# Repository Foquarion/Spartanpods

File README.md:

# Spartanpods Logo PCB Variations
Use Version 2 as the production model

# Version Description:
  - Version 1 is the original wave text version
  - Version 2 is the SQUARE PCB version (USE THIS ONE)
  - Version 3 is an incomplete start for a Helmet ONLY version. I have not completed it (no circuit) but the PCB is there for you to use

# To Do For You (Max):
Confirm SWITCH positioning
  - If alternate switch used, be aware of "Through-Hole nubs" on most other SMD switches (holes will be visible from the other side)
    
Phototransistor position
  - I did not leave the phototransistor overhanging over the edge, so be aware plaving it down will ~always appear as night-light active mode (I did this to leave a clean edge)
      + Adjust position to overhang if not desired
   
Battery:
  - Currently using a CR2032 coin cell because I already had the circuit done
  - Could probably fit AA or AAAs on here instead (or even a 9v adapter and use that as built-in stand)

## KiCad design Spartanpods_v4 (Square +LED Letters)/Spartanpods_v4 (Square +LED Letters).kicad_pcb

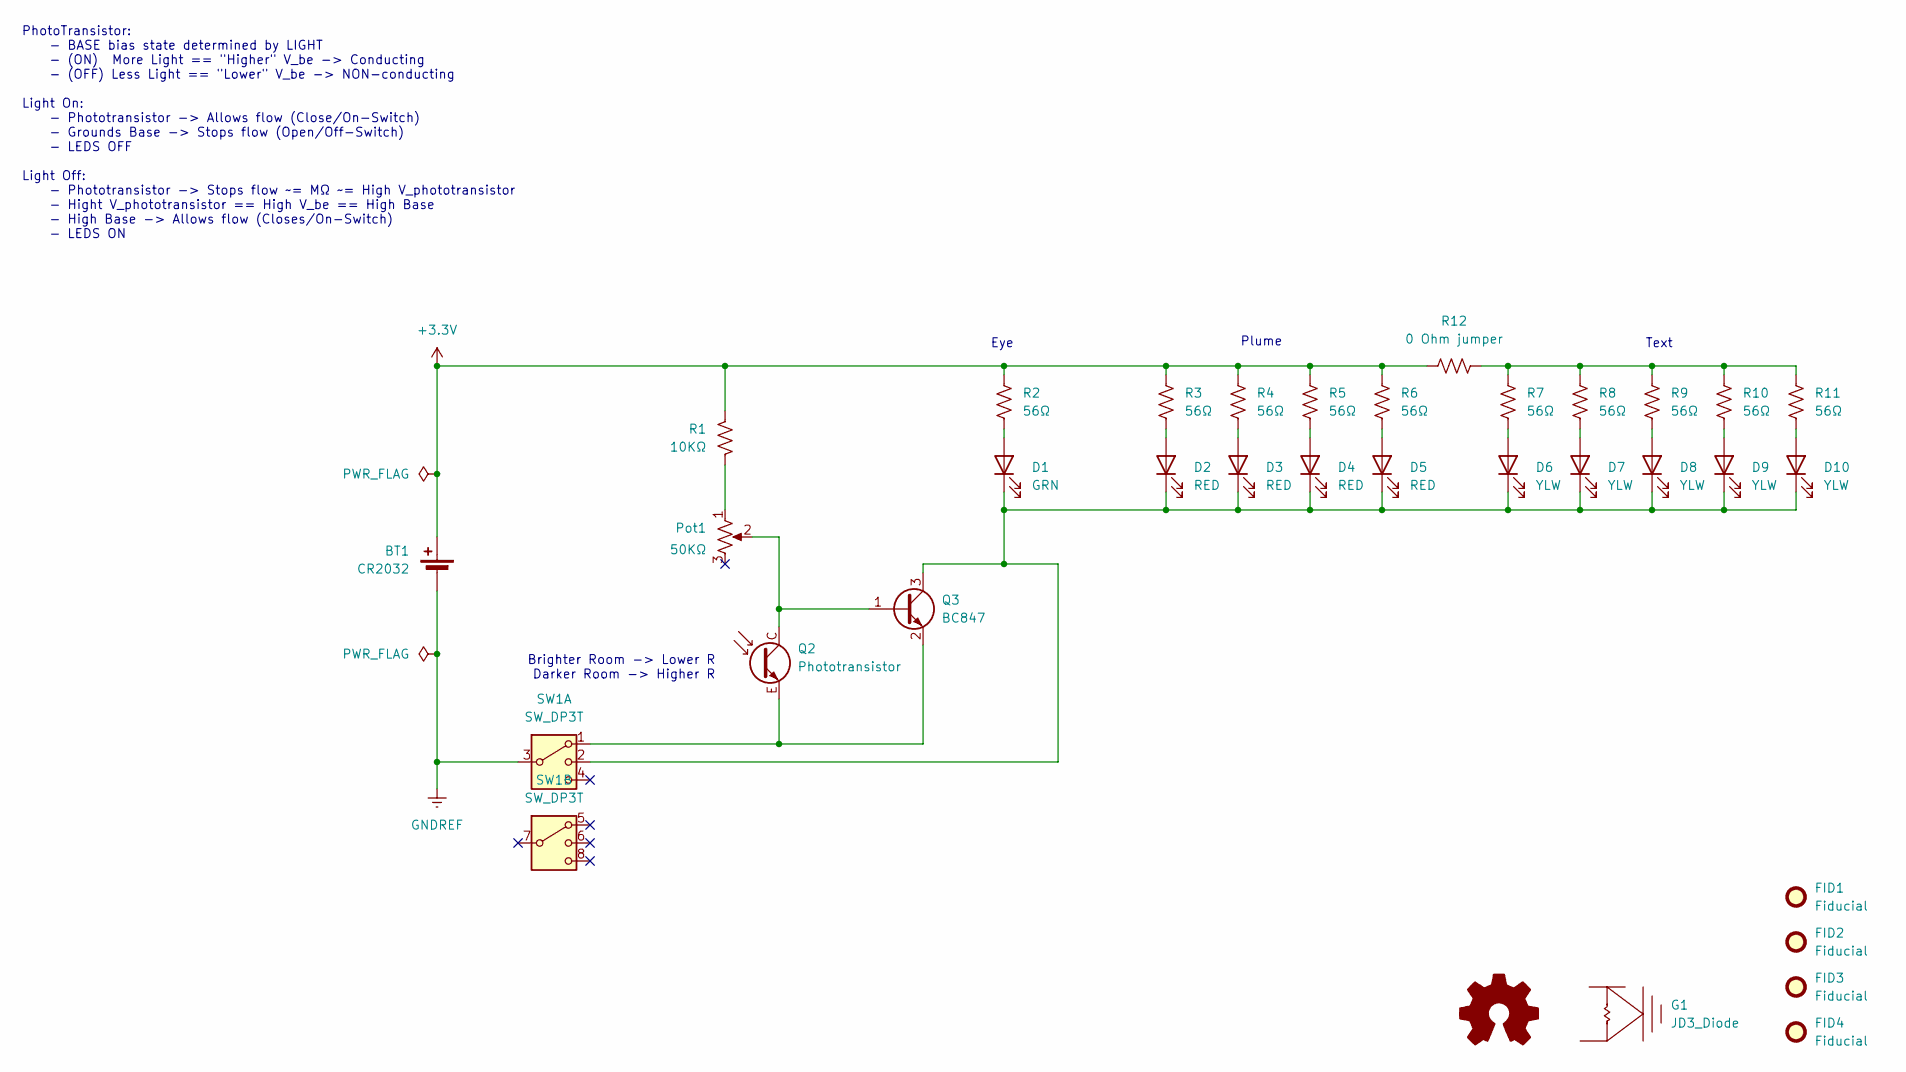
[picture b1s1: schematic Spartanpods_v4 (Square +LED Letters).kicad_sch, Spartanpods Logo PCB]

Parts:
BT1: CR2032; CR2032-Holder; MFG P/N BH-49A-5
D1: GRN; LED - MyPLCC2 (RoundMask_LED Side); MFG P/N XZDGK45WT-9
D2, D3, D4, D5: RED; LED - MyPLCC2 (RoundMask_LED Side); MFG P/N XZM2CRK45WT-9
D6, D7, D8, D9, D10: YLW; LED - MyPLCC2 (RoundMask_LED Side); MFG P/N XZM2CRK45WT-9
FID1, FID2, FID3, FID4: Fiducial; Fiducial_0.75mm_Mask2.25mm
G1: JD3_Diode
G2: Logo_Open_Hardware_Small; Combined_LED Text
Pot1: 50KΩ; Potentiometer_Bourns_TC33X_Vertical; MFG P/N TC33X-2-503E
Q2: Phototransistor; PhotoTrans_PT12-21C_TR8 (Flipped); MFG P/N PT12-21C/TR8
Q3: BC847; SOT-23; MFG P/N BC847B,215
R1: 10KΩ; C_0603_1608Metric_Pad1.08x0.95mm_HandSolder; MFG P/N ESR03EZPJ103
R2, R3, R4, R5, R6, R7, R8, R9, R10, R11: 56Ω; C_0805_2012Metric_Pad1.18x1.45mm_HandSolder; MFG P/N RC0805JR-0756RL
R12: 0 Ohm jumper; R_0805_2012Metric_Pad1.20x1.40mm_HandSolder
SW1: SW_DP3T; DP3T - JS203011SCQN; MFG P/N JS203011SCQN

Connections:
+3.3V: BT1.1 (Pos), R1.2, R2.1, R3.1, R4.1, R5.1, R6.1, R12.1
GNDREF: BT1.2 (Neg), SW1.3
unnamed: D1.2 (A), R2.2
unnamed: D1.1 (K), D2.1 (K), D3.1 (K), D4.1 (K), D5.1 (K), D6.1 (K), D7.1 (K), D8.1 (K), D9.1 (K), D10.1 (K), Q3.3 (C), SW1.2
unnamed: D2.2 (A), R3.2
unnamed: D3.2 (A), R4.2
unnamed: D4.2 (A), R5.2
unnamed: D5.2 (A), R6.2
unnamed: D6.2 (A), R7.2
unnamed: D7.2 (A), R8.2
unnamed: D8.2 (A), R9.2
unnamed: D9.2 (A), R10.2
unnamed: D10.2 (A), R11.2
unnamed: Pot1.1, R1.1
unnamed: Pot1.2, Q2.C (1), Q3.1 (B)
unnamed: Q2.E (2), Q3.2 (E), SW1.1
unnamed: R7.1, R8.1, R9.1, R10.1, R11.1, R12.2

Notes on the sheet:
Eye
Brighter Room -> Lower R Darker Room -> Higher R
Text
PhotoTransistor: - BASE bias state determined by LIGHT - (ON) More Light == "Higher" V_be -> Conducting - (OFF) Less Light == "Lower" V_be -> NON-conducting Light On: - Phototransistor -> Allows flow (Close/On-Switch) - Grounds Base -> Stops flow (Open/Off-Switch) - LEDS OFF Light Off: - Phototrans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
Plume

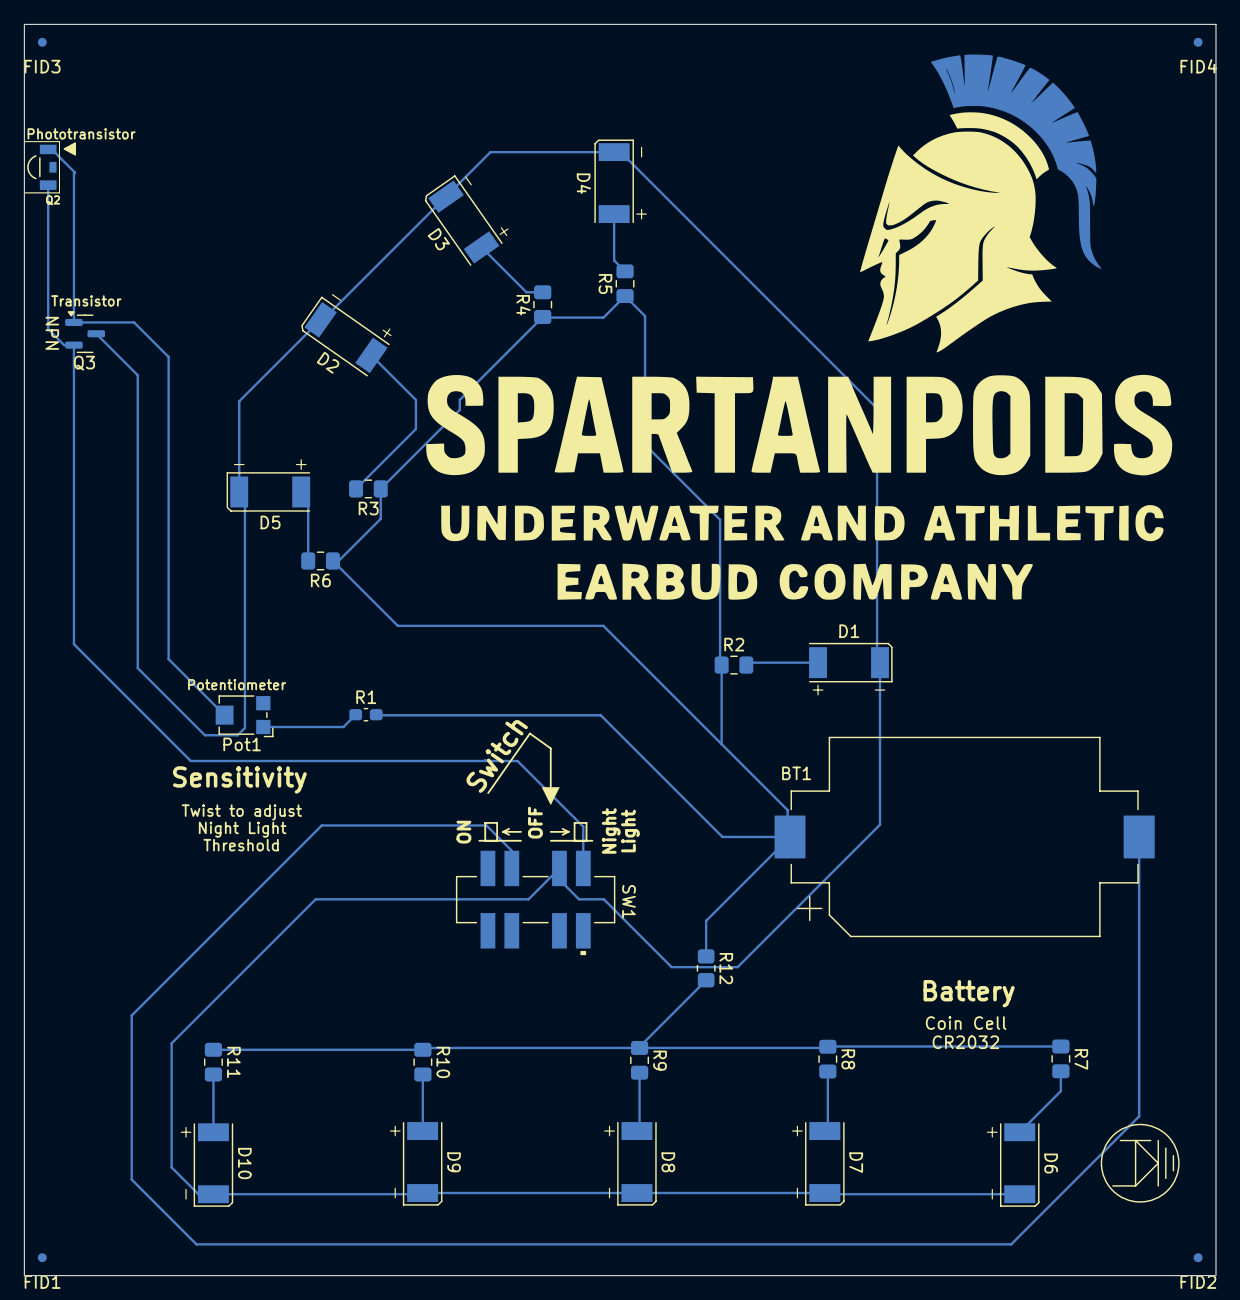
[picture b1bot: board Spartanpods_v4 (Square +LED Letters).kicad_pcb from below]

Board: 2 copper layers, 100.0 x 105.0 mm, 33 parts (32 on the bottom side), 17 nets.

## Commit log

2025-12-16 Included Library Package
2025-12-16 Add README for Spartanpods Logo PCB Variations
2025-12-16 Fix formatting in README.md for version descriptions
2025-12-16 Full Library Update
2025-12-16 Inkscape additions
2025-12-17 Spartanpods v4
2025-12-17 Tidy
